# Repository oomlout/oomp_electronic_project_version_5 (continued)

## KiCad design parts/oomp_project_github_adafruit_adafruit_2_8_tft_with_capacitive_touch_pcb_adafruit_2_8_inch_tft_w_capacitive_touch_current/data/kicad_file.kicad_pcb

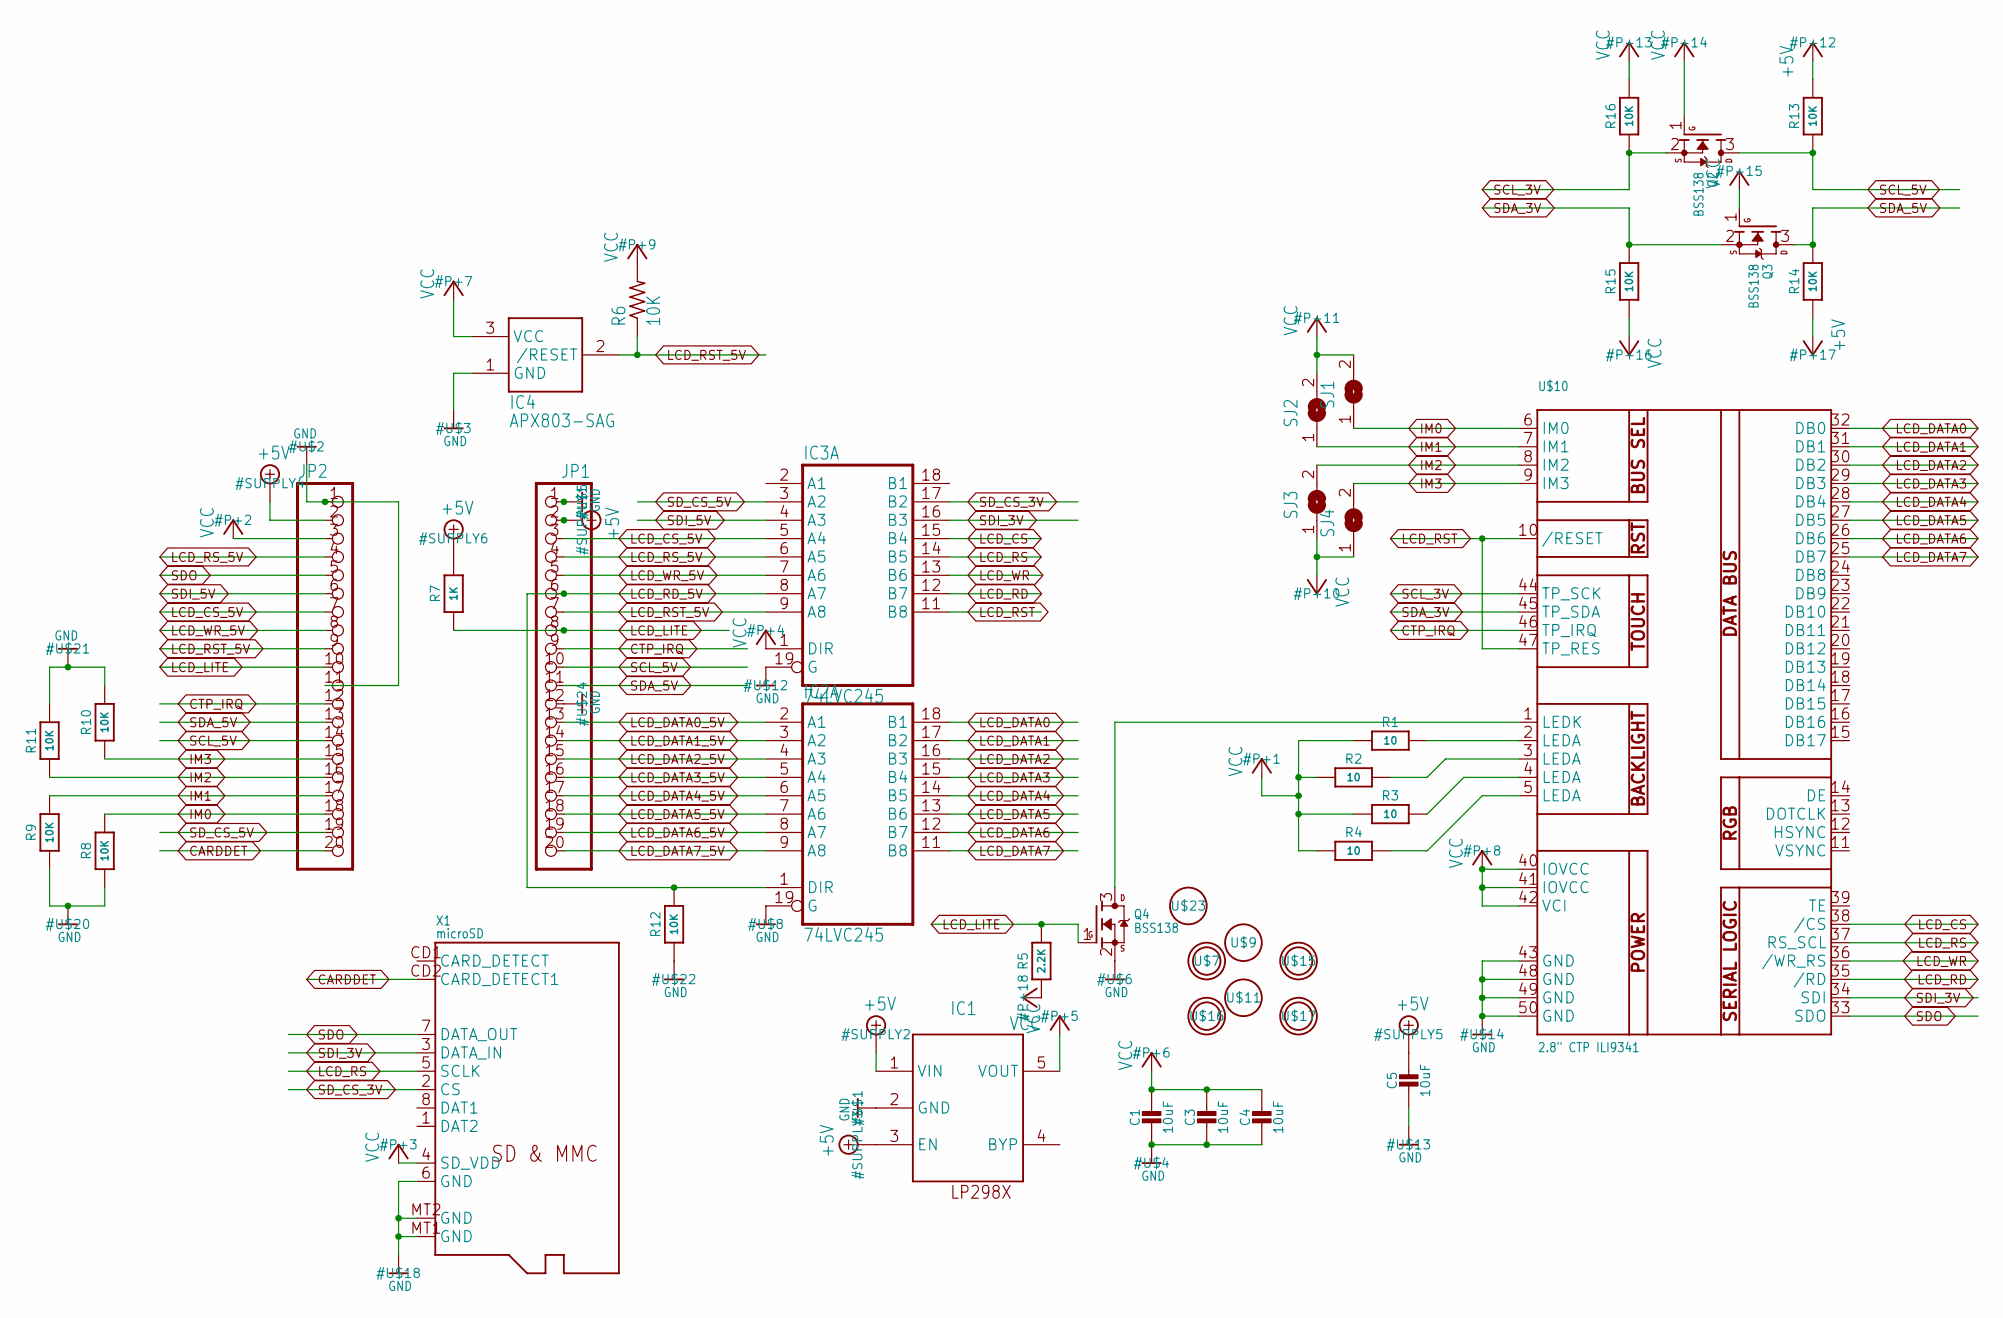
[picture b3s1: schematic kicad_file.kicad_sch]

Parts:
C1, C3, C4, C5: 10uF; 0805-NO
IC1: MIC5225-3.3; SOT23-5L
IC2, IC3: 74LVC245; SO20W
IC4: APX803-SAG; SOT23
JP1, JP2: HEADER-1X20ROUND; 1X20_ROUND
Q2, Q3, Q4: BSS138; SOT23-WIDE
R1, R2, R3, R4: 10; 0805-NO
R5: 2.2K; 0805-NO
R6: 10K; R0805
R7: 1K; 0805-NO
R8, R9, R10, R11, R12, R13, R14, R15, R16: 10K; 0805-NO
SJ1, SJ2, SJ3, SJ4: SOLDERJUMPER; SOLDERJUMPER_ARROW_NOPASTE
U$7, U$15, U$16, U$17: MOUNTINGHOLE3.0THIN; MOUNTINGHOLE_3.0_PLATEDTHIN
U$9, U$11, U$23: FIDUCIAL; FIDUCIAL_1MM
U$10: 2.8" CTP ILI9341; TFT_2.83IN_240X320_50PIN
X1: microSD; MICROSD

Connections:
+5V: C5.1, IC1.1 (VIN), IC1.3 (EN), JP1.2, JP2.2, R7.2, R13.2, R14.1
CARDDET: JP2.20, X1.CD2 (CARD_DETECT1)
CTP_IRQ: JP1.9, JP2.12, U$10.46 (TP_IRQ)
GND: C1.2, C3.2, C4.2, C5.2, IC1.2 (GND), IC2.10 (GND), IC2.19 (G), IC3.10 (GND), IC3.19 (G), IC4.1 (GND), JP1.1, JP1.12, JP2.1, JP2.11, Q4.2 (S), R8.1, R9.1, R10.2, R11.2, R12.1, U$10.43 (GND), U$10.48 (GND), U$10.49 (GND), U$10.50 (GND), X1.6 (GND), X1.MT1 (GND), X1.MT2 (GND)
IM0: JP2.18, R8.2, SJ1.1, U$10.6 (IM0)
IM1: JP2.17, R9.2, SJ2.1, U$10.7 (IM1)
IM2: JP2.16, R11.1, SJ3.2, U$10.8 (IM2)
IM3: JP2.15, R10.1, SJ4.2, U$10.9 (IM3)
LCD_CS: IC3.15 (B4), U$10.38 (/CS)
LCD_CS_5V: IC3.5 (A4), JP1.3, JP2.7
LCD_DATA0: IC2.18 (B1), U$10.32 (DB0)
LCD_DATA0_5V: IC2.2 (A1), JP1.13
LCD_DATA1: IC2.17 (B2), U$10.31 (DB1)
LCD_DATA1_5V: IC2.3 (A2), JP1.14
LCD_DATA2: IC2.16 (B3), U$10.30 (DB2)
LCD_DATA2_5V: IC2.4 (A3), JP1.15
LCD_DATA3: IC2.15 (B4), U$10.29 (DB3)
LCD_DATA3_5V: IC2.5 (A4), JP1.16
LCD_DATA4: IC2.14 (B5), U$10.28 (DB4)
LCD_DATA4_5V: IC2.6 (A5), JP1.17
LCD_DATA5: IC2.13 (B6), U$10.27 (DB5)
LCD_DATA5_5V: IC2.7 (A6), JP1.18
LCD_DATA6: IC2.12 (B7), U$10.26 (DB6)
LCD_DATA6_5V: IC2.8 (A7), JP1.19
LCD_DATA7: IC2.11 (B8), U$10.25 (DB7)
LCD_DATA7_5V: IC2.9 (A8), JP1.20
LCD_LITE: JP1.8, JP2.10, Q4.1 (G), R5.2, R7.1
LCD_RD: IC3.12 (B7), U$10.35 (/RD)
LCD_RD_5V: IC2.1 (DIR), IC3.8 (A7), JP1.6, R12.2
LCD_RS: IC3.14 (B5), U$10.37 (RS_SCL), X1.5 (SCLK)
LCD_RST: IC3.11 (B8), U$10.10 (/RESET), U$10.47 (TP_RES)
LCD_RST_5V: IC3.9 (A8), IC4.2 (/RESET), JP1.7, JP2.9, R6.1
LCD_RS_5V: IC3.6 (A5), JP1.4, JP2.4
LCD_WR: IC3.13 (B6), U$10.36 (/WR_RS)
LCD_WR_5V: IC3.7 (A6), JP1.5, JP2.8
unnamed: R4.2, U$10.5 (LEDA)
unnamed: R1.2, U$10.2 (LEDA)
unnamed: R2.2, U$10.3 (LEDA)
unnamed: R3.2, U$10.4 (LEDA)
unnamed: Q4.3 (D), U$10.1 (LEDK)
SCL_3V: Q2.2 (S), R16.1, U$10.44 (TP_SCK)
SCL_5V: JP1.10, JP2.14, Q2.3 (D), R13.1
SDA_3V: Q3.2 (S), R15.2, U$10.45 (TP_SDA)
SDA_5V: JP1.11, JP2.13, Q3.3 (D), R14.2
SDI_3V: IC3.16 (B3), U$10.34 (SDI), X1.3 (DATA_IN)
SDI_5V: IC3.4 (A3), JP2.6
SDO: JP2.5, U$10.33 (SDO), X1.7 (DATA_OUT)
SD_CS_3V: IC3.17 (B2), X1.2 (CS)
SD_CS_5V: IC3.3 (A2), JP2.19
VCC: C1.1, C3.1, C4.1, IC1.5 (VOUT), IC2.20 (VCC), IC3.1 (DIR), IC3.20 (VCC), IC4.3 (VCC), JP2.3, Q2.1 (G), Q3.1 (G), R1.1, R2.1, R3.1, R4.1, R5.1, R6.2, R15.1, R16.2, SJ1.2, SJ2.2, SJ3.1, SJ4.1, U$10.40 (IOVCC), U$10.41 (IOVCC), U$10.42 (VCI), X1.4 (SD_VDD)

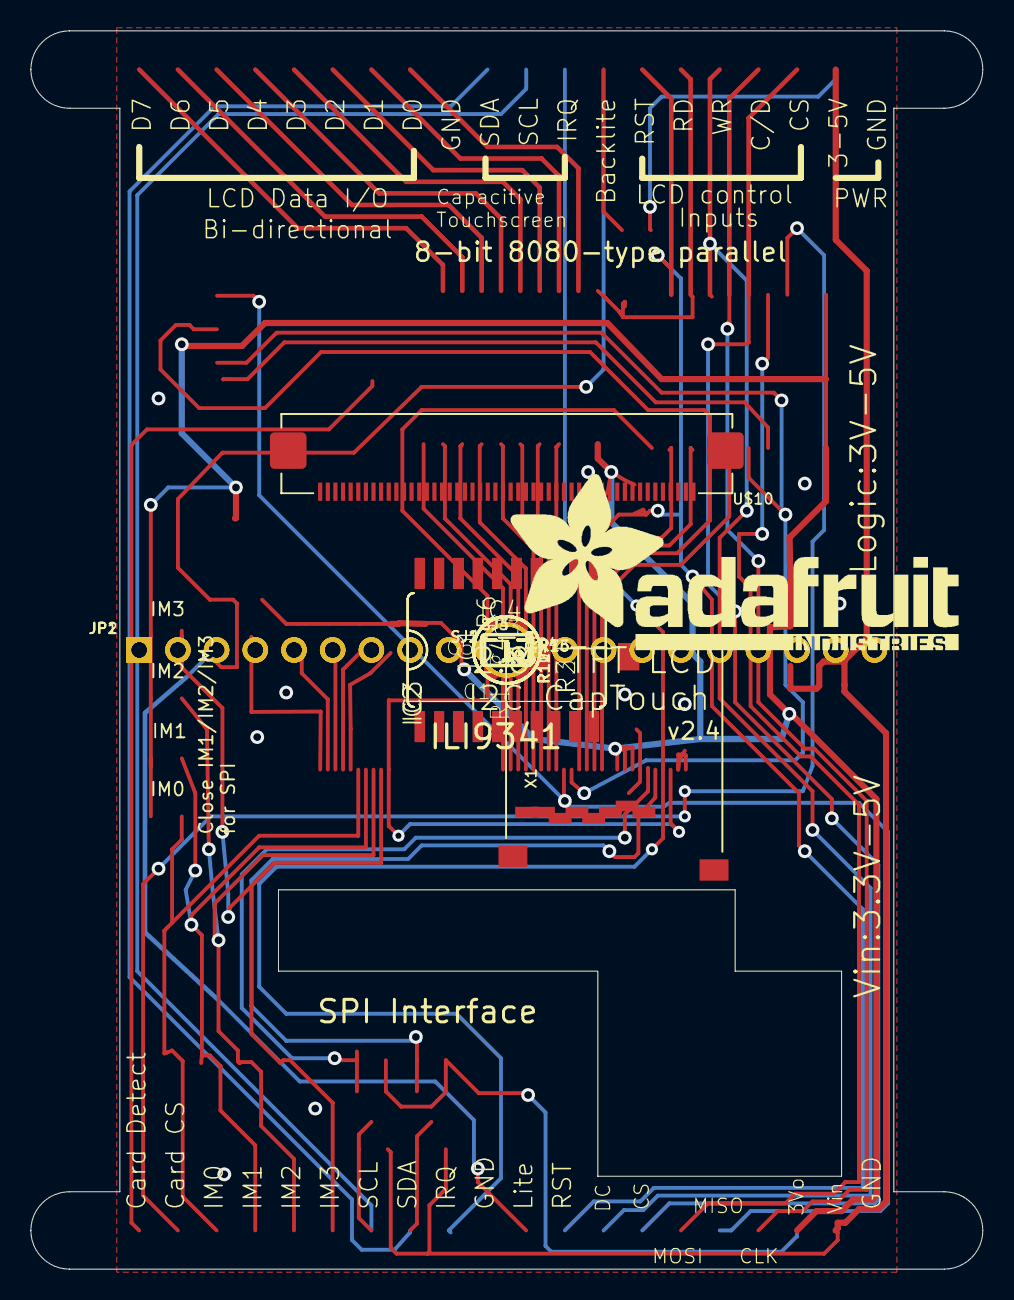
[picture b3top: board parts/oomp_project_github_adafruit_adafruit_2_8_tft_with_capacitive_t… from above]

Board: 16 copper layers, 62.5 x 81.3 mm, 43 parts (1 on the bottom side), 50 nets.

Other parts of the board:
U$19: ADAFRUIT_TEXT_30MM

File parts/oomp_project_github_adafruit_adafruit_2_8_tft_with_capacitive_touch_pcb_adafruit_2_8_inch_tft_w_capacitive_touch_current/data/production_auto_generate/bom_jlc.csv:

Comment,Designator,Footprint,LCSC Part #
,"JP1,JP2",Adafruit 2.8 inch TFT w Capacitive Touch-import-fps:1X20_ROUND,C50981
,U$19,Adafruit 2.8 inch TFT w Capacitive Touch-import-fps:ADAFRUIT_TEXT_30MM,
10,"R1,R2,R3,R4",Adafruit 2.8 inch TFT w Capacitive Touch-import-fps:0805-NO,C17415
10K,"R8,R9,R10,R11,R12,R13,R14,R15,R16",Adafruit 2.8 inch TFT w Capacitive Touch-import-fps:0805-NO,C17414
10K,R6,Adafruit 2.8 inch TFT w Capacitive Touch-import-fps:R0805,C17414
10uF,"C1,C3,C4,C5",Adafruit 2.8 inch TFT w Capacitive Touch-import-fps:0805-NO,
1K,R7,Adafruit 2.8 inch TFT w Capacitive Touch-import-fps:0805-NO,C17513
2.2K,R5,Adafruit 2.8 inch TFT w Capacitive Touch-import-fps:0805-NO,C17520
"2.8"" CTP ILI9341",U$10,Adafruit 2.8 inch TFT w Capacitive Touch-import-fps:TFT_2.83IN_240X320_50PIN,
74LVC245,"IC2,IC3",Adafruit 2.8 inch TFT w Capacitive Touch-import-fps:SO20W,
APX803-SAG,IC4,Adafruit 2.8 inch TFT w Capacitive Touch-import-fps:SOT23,
BSS138,"Q2,Q3,Q4",Adafruit 2.8 inch TFT w Capacitive Touch-import-fps:SOT23-WIDE,C52895
FIDUCIAL,"U$9,U$11,U$23",Adafruit 2.8 inch TFT w Capacitive Touch-import-fps:FIDUCIAL_1MM,
MIC5225-3.3,IC1,Adafruit 2.8 inch TFT w Capacitive Touch-import-fps:SOT23-5L,
microSD,X1,Adafruit 2.8 inch TFT w Capacitive Touch-import-fps:MICROSD,
